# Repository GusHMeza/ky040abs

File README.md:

# ky040abs
Turn a KY040 incremental encoder to an absolute encoder with a 1 wire interface.
The KiCAD project is provided for the adapter board. 

IMPORTANT: Use avrboy by kimio-kosaka to program the ATTINY10 chip before soldering it to this adapter module. The PCB does not have a TPI interface connector.

# HOW TO USE
1. Flash an ATTINY10 chip with the provided script.
2. Use the suggested connector in the BOM or solder wires to the power inputs and the signal wire.
3. Power the module.
4. The SIG wire works as an active HIGH input, when it receives a HIGH pulse, it switches to an active HIGH output. I.e. use an I/O pin from a MCU to pulse the SIG wire, then read how many pulses the ky040abs answers with.
5. To adjust the resolution (given you have a gear ratio between the encoder and and a spinning shaft), modify the *angulo_en_pulsos* variable.
6. The provided code shows a bidirectional rotation reading, where the ATTINY10 starts at 15 counts that either increment up to 30 or decrement down to 0 depending on the direction of rotation.

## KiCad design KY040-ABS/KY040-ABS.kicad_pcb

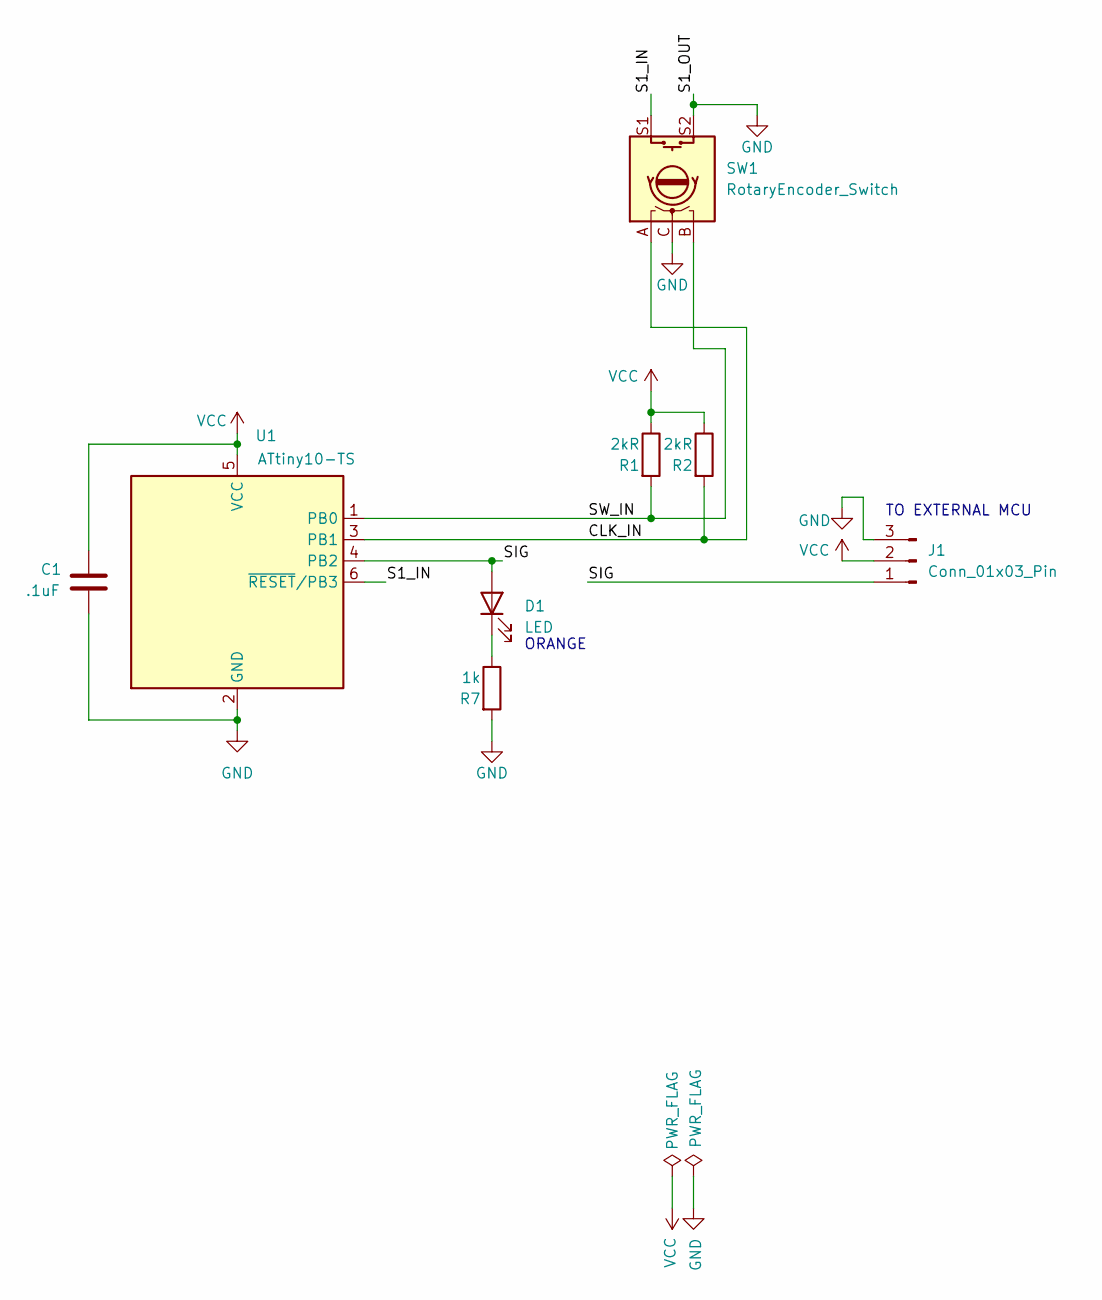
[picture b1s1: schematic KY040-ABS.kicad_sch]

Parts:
C1: .1uF; C_0603_1608Metric
D1: LED; LED_0603_1608Metric
J1: Conn_01x03_Pin; JST_PH_S3B-PH-K_1x03_P2.00mm_Horizontal
R1, R2: 2kR; R_0603_1608Metric
R7: 1k; R_0603_1608Metric
SW1: RotaryEncoder_Switch; RotaryEncoder_Alps_EC11E-Switch_Vertical_H20mm_CircularMoun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
U1: ATtiny10-TS; SOT-23-6

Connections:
/CLK_IN: R2.2, SW1.A, U1.3 (PB1)
/S1_IN: SW1.S1, U1.6 (~RESET/PB3)
/SIG: D1.2 (A), J1.1, U1.4 (PB2)
/SW_IN: R1.2, SW1.B, U1.1 (PB0)
GND: C1.2, J1.3, R7.2, SW1.C, SW1.S2, U1.2 (GND)
unnamed: D1.1 (K), R7.1
VCC: C1.1, J1.2, R1.1, R2.1, U1.5 (VCC)

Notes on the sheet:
ORANGE
TO EXTERNAL MCU

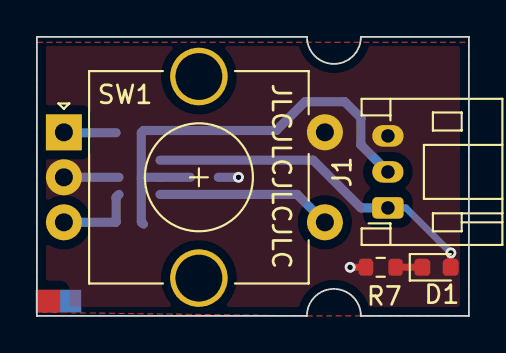
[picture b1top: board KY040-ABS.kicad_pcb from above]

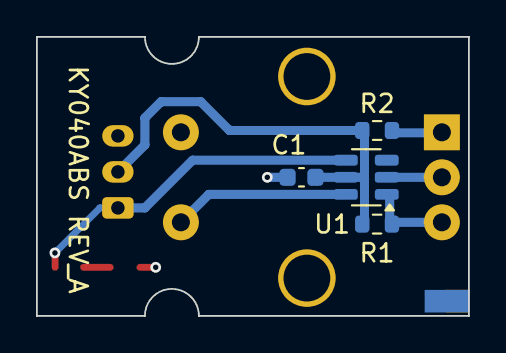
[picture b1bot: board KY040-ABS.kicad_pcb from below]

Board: 2 copper layers, 24.0 x 15.5 mm, 8 parts (4 on the bottom side), 7 nets.

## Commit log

2024-09-10 Source code written in cpp
2024-09-10 Added pictures
2024-09-10 Commit RevA
2026-01-12 Format readme
